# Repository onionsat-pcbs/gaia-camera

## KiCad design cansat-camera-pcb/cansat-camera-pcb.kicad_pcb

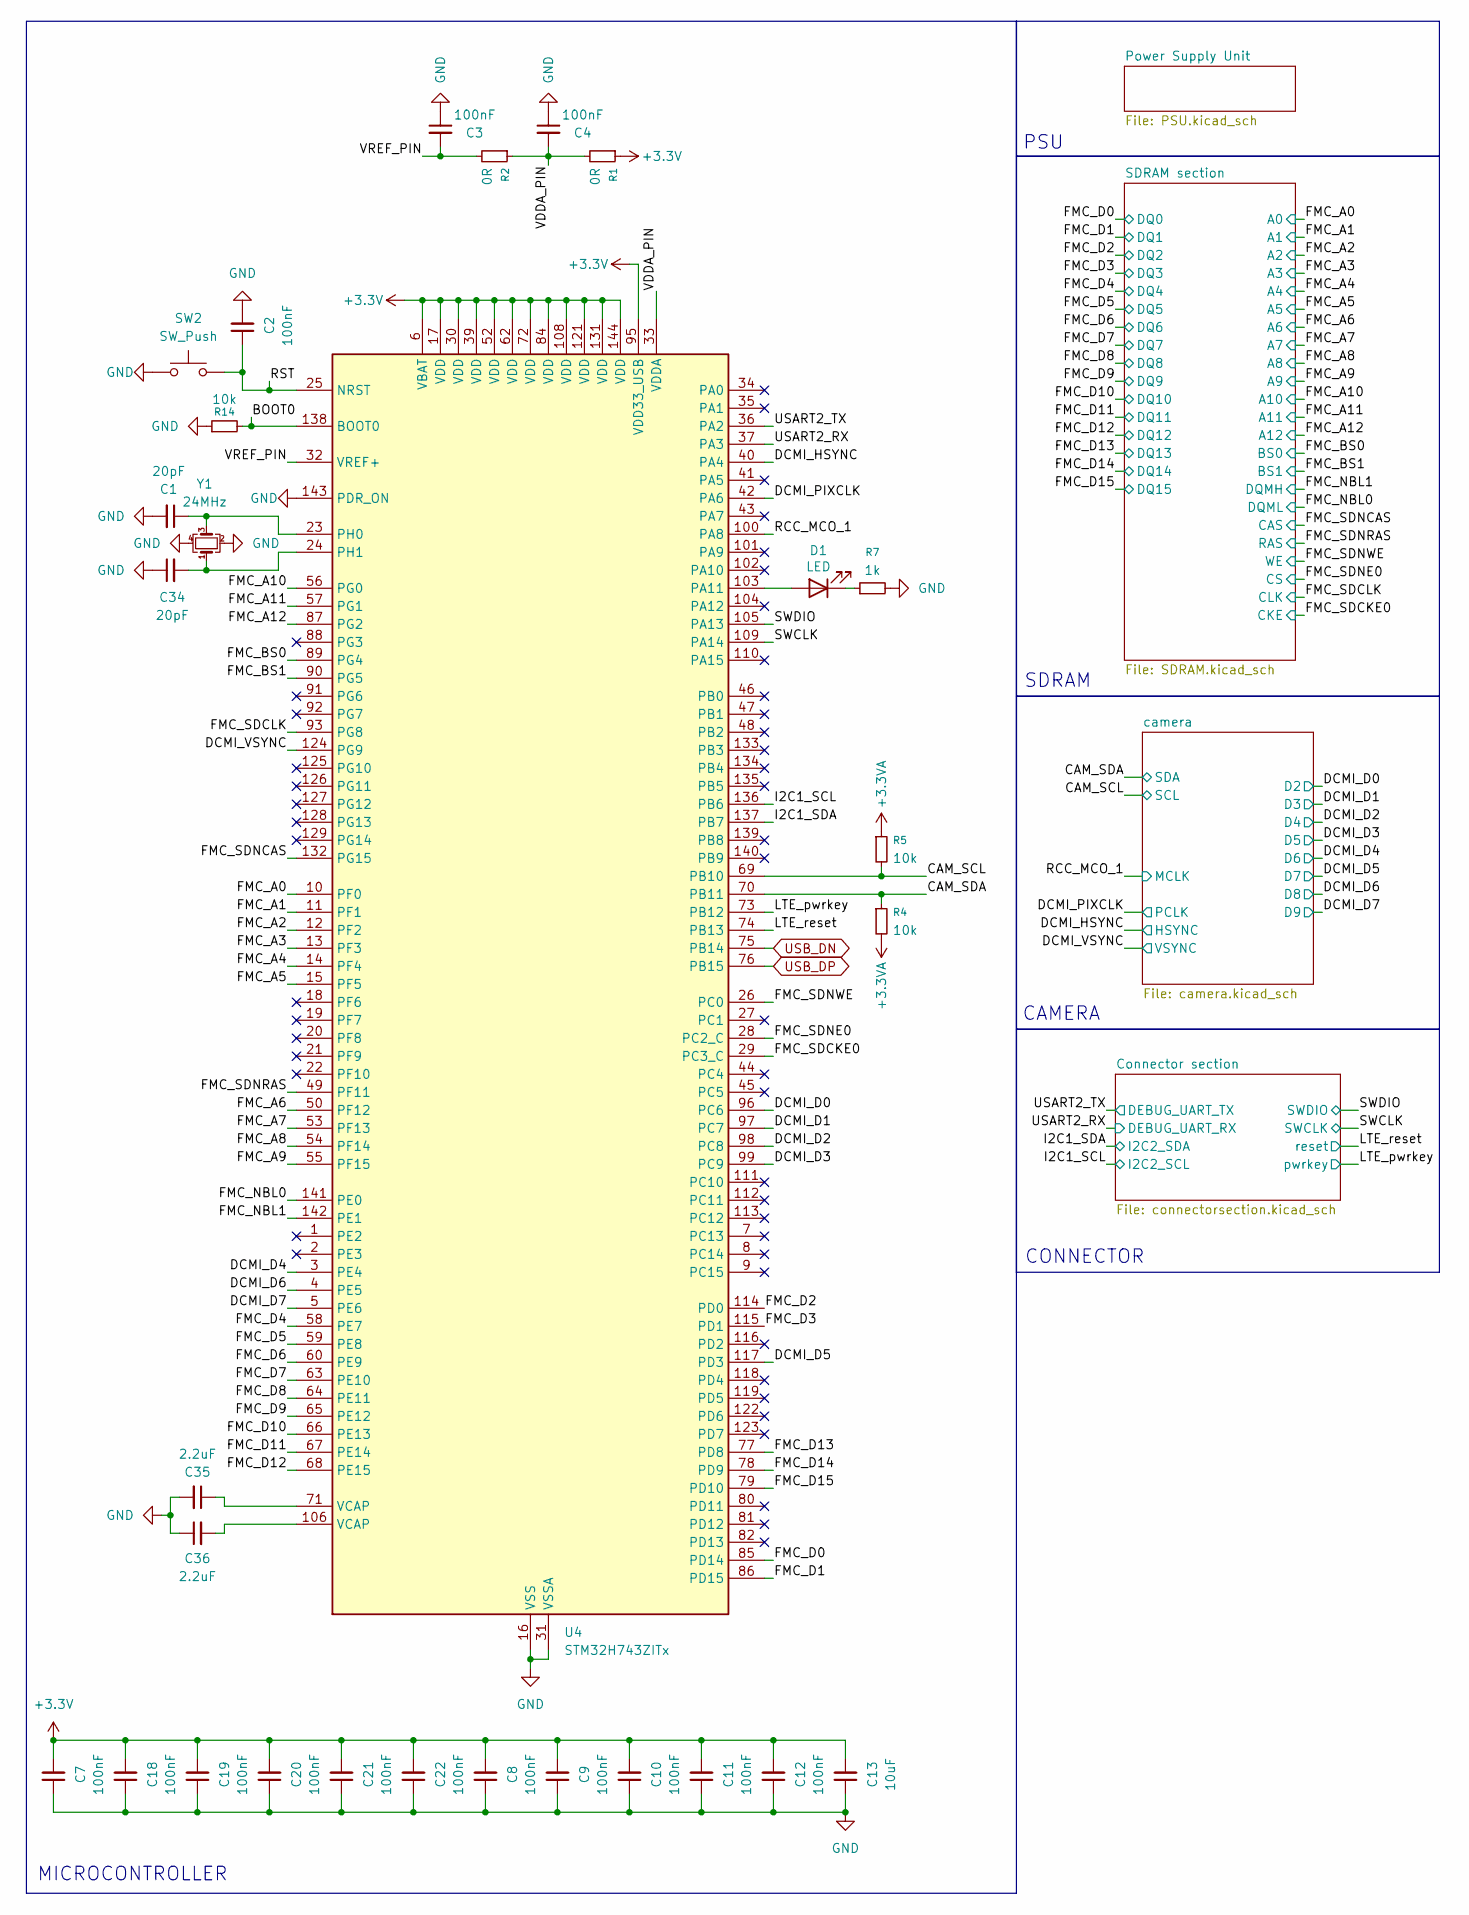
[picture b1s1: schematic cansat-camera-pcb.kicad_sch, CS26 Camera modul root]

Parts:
C1, C34: 20pF; C_0402_1005Metric
C2, C3, C4, C7, C8, C9, C10, C11, C12, C18, C19, C20, C21, C22: 100nF; C_0402_1005Metric
C13: 10uF; C_0603_1608Metric
C35, C36: 2.2uF; C_0603_1608Metric
D1: LED; LED_0603_1608Metric
R1, R2: 0R; R_0402_1005Metric
R4, R5, R14: 10k; R_0402_1005Metric
R7: 1k; R_0603_1608Metric
SW2: SW_Push; KEY-SMD_L4.0-W3.0-LS4.9-1
U4: STM32H743ZITx; LQFP-144_20x20mm_P0.5mm
Y1: 24MHz; Crystal_SMD_3225-4Pin_3.2x2.5mm

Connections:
+3.3V: C7.2, C8.2, C9.2, C10.2, C11.2, C12.2, C13.2, C18.2, C19.2, C20.2, C21.2, C22.2, R1.1, U4.6 (VBAT), U4.17 (VDD), U4.30 (VDD), U4.39 (VDD), U4.52 (VDD), U4.62 (VDD), U4.72 (VDD), U4.84 (VDD), U4.95 (VDD33_USB), U4.108 (VDD), U4.121 (VDD), U4.131 (VDD), U4.144 (VDD); also elsewhere on the board
+3.3VA: R4.2, R5.1; also elsewhere on the board
/BOOT0: R14.2, U4.138 (BOOT0)
/CAM_SCL: R5.2, U4.69 (PB10); also elsewhere on the board
/CAM_SDA: R4.1, U4.70 (PB11); also elsewhere on the board
/DCMI_D0: U4.96 (PC6); also elsewhere on the board
/DCMI_D1: U4.97 (PC7); also elsewhere on the board
/DCMI_D2: U4.98 (PC8); also elsewhere on the board
/DCMI_D3: U4.99 (PC9); also elsewhere on the board
/DCMI_D4: U4.3 (PE4); also elsewhere on the board
/DCMI_D5: U4.117 (PD3); also elsewhere on the board
/DCMI_D6: U4.4 (PE5); also elsewhere on the board
/DCMI_D7: U4.5 (PE6); also elsewhere on the board
/DCMI_HSYNC: U4.40 (PA4); also elsewhere on the board
/DCMI_PIXCLK: U4.42 (PA6); also elsewhere on the board
/DCMI_VSYNC: U4.124 (PG9); also elsewhere on the board
/FMC_A0: U4.10 (PF0); also elsewhere on the board
/FMC_A1: U4.11 (PF1); also elsewhere on the board
/FMC_A2: U4.12 (PF2); also elsewhere on the board
/FMC_A3: U4.13 (PF3); also elsewhere on the board
/FMC_A4: U4.14 (PF4); also elsewhere on the board
/FMC_A5: U4.15 (PF5); also elsewhere on the board
/FMC_A6: U4.50 (PF12); also elsewhere on the board
/FMC_A7: U4.53 (PF13); also elsewhere on the board
/FMC_A8: U4.54 (PF14); also elsewhere on the board
/FMC_A9: U4.55 (PF15); also elsewhere on the board
/FMC_A10: U4.56 (PG0); also elsewhere on the board
/FMC_A11: U4.57 (PG1); also elsewhere on the board
/FMC_A12: U4.87 (PG2); also elsewhere on the board
/FMC_BS0: U4.89 (PG4); also elsewhere on the board
/FMC_BS1: U4.90 (PG5); also elsewhere on the board
/FMC_D0: U4.85 (PD14); also elsewhere on the board
/FMC_D1: U4.86 (PD15); also elsewhere on the board
/FMC_D2: U4.114 (PD0); also elsewhere on the board
/FMC_D3: U4.115 (PD1); also elsewhere on the board
/FMC_D4: U4.58 (PE7); also elsewhere on the board
/FMC_D5: U4.59 (PE8); also elsewhere on the board
/FMC_D6: U4.60 (PE9); also elsewhere on the board
/FMC_D7: U4.63 (PE10); also elsewhere on the board
/FMC_D8: U4.64 (PE11); also elsewhere on the board
/FMC_D9: U4.65 (PE12); also elsewhere on the board
/FMC_D10: U4.66 (PE13); also elsewhere on the board
/FMC_D11: U4.67 (PE14); also elsewhere on the board
/FMC_D12: U4.68 (PE15); also elsewhere on the board
/FMC_D13: U4.77 (PD8); also elsewhere on the board
/FMC_D14: U4.78 (PD9); also elsewhere on the board
/FMC_D15: U4.79 (PD10); also elsewhere on the board
/FMC_NBL0: U4.141 (PE0); also elsewhere on the board
/FMC_NBL1: U4.142 (PE1); also elsewhere on the board
/FMC_SDCKE0: U4.29 (PC3_C); also elsewhere on the board
/FMC_SDCLK: U4.93 (PG8); also elsewhere on the board
/FMC_SDNCAS: U4.132 (PG15); also elsewhere on the board
/FMC_SDNE0: U4.28 (PC2_C); also elsewhere on the board
/FMC_SDNRAS: U4.49 (PF11); also elsewhere on the board
/FMC_SDNWE: U4.26 (PC0); also elsewhere on the board
/I2C1_SCL: U4.136 (PB6); also elsewhere on the board
/I2C1_SDA: U4.137 (PB7); also elsewhere on the board
/LTE_pwrkey: U4.73 (PB12); also elsewhere on the board
/LTE_reset: U4.74 (PB13); also elsewhere on the board
/RCC_MCO_1: U4.100 (PA8); also elsewhere on the board
/RST: C2.1, SW2.2, U4.25 (NRST)
/SWCLK: U4.109 (PA14); also elsewhere on the board
/SWDIO: U4.105 (PA13); also elsewhere on the board
/USART2_RX: U4.37 (PA3); also elsewhere on the board
/USART2_TX: U4.36 (PA2); also elsewhere on the board
/VDDA_PIN: C4.2, R1.2, R2.1, U4.33 (VDDA)
/VREF_PIN: C3.2, R2.2, U4.32 (VREF+)
GND: C1.2, C2.2, C3.1, C4.1, C7.1, C8.1, C9.1, C10.1, C11.1, C12.1, C13.1, C18.1, C19.1, C20.1, C21.1, C22.1, C34.1, C35.2, C36.1, R7.2, R14.1, SW2.1, U4.16 (VSS), U4.31 (VSSA), U4.38 (VSS), U4.51 (VSS), U4.61 (VSS), U4.83 (VSS), U4.94 (VSS), U4.107 (VSS), U4.120 (VSS), U4.130 (VSS), U4.143 (PDR_ON), Y1.2, Y1.4; also elsewhere on the board
unnamed: C35.1, U4.71 (VCAP)
unnamed: C36.2, U4.106 (VCAP)
unnamed: D1.2 (A), U4.103 (PA11)
unnamed: D1.1 (K), R7.1
unnamed: C1.1, U4.23 (PH0), Y1.3
unnamed: C34.2, U4.24 (PH1), Y1.1
USB_DN: U4.75 (PB14); also elsewhere on the board
USB_DP: U4.76 (PB15); also elsewhere on the board

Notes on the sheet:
PSU
SDRAM
MICROCONTROLLER
CAMERA
CONNECTOR

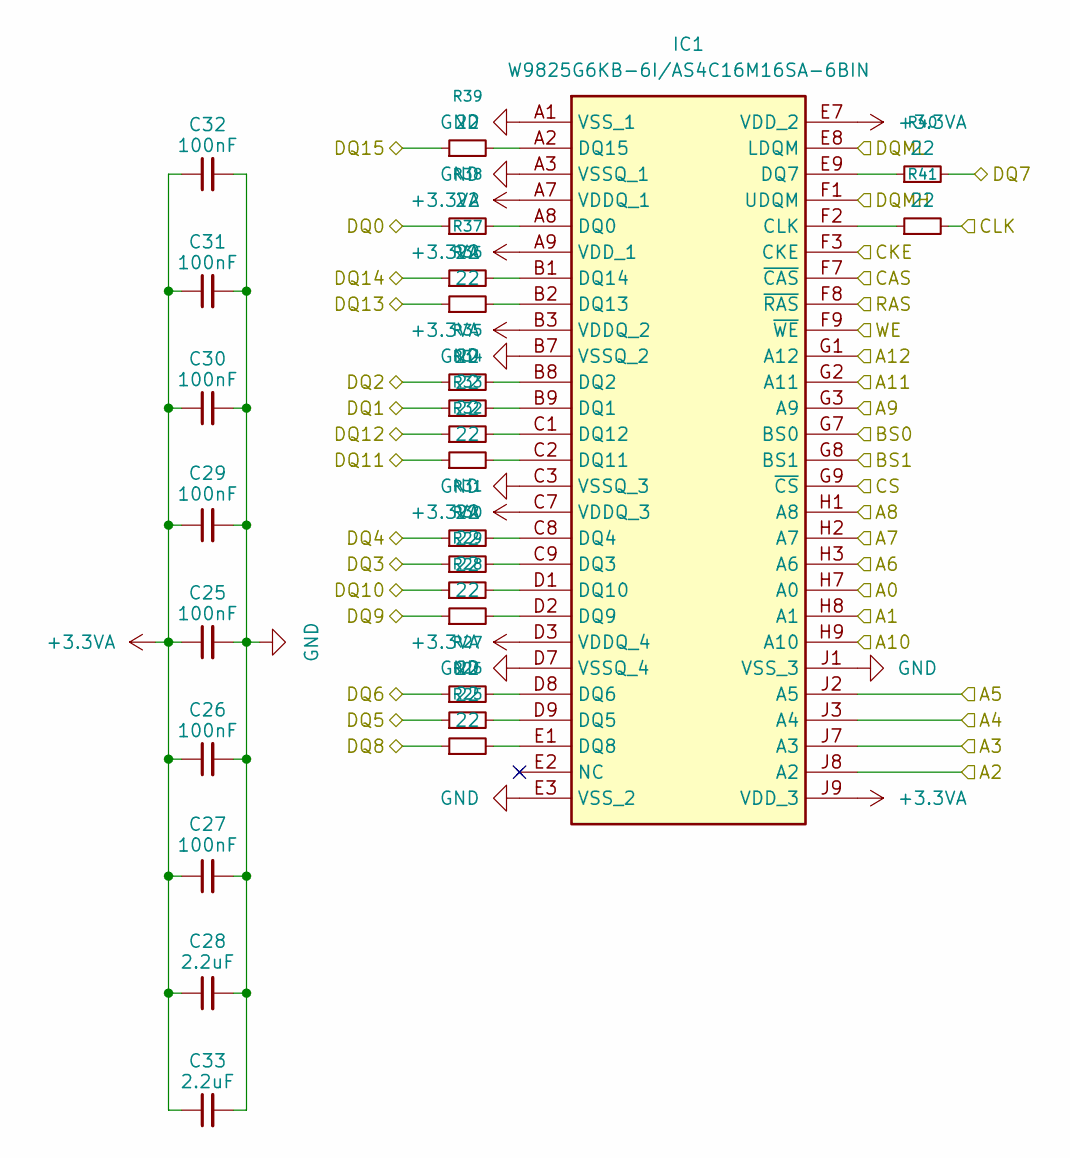
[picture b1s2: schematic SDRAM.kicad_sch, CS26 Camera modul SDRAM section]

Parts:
C25, C26, C27, C29, C30, C31, C32: 100nF; C_0402_1005Metric
C28, C33: 2.2uF; C_0603_1608Metric
IC1: W9825G6KB-6I/AS4C16M16SA-6BIN; Alliance_TFBGA-54_8x8mm_Layout9x9_P0.8mm; Mouser Part Number 454-W9825G6JB-6I
R25, R26, R27, R28, R29, R30, R31, R32, R33, R34, R35, R36, R37, R38, R39, R40, R41: 22; R_0201_0603Metric

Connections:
+3.3VA: C25.1, C26.1, C27.1, C28.1, C29.1, C30.1, C31.1, C32.1, C33.1, IC1.A7 (VDDQ_1), IC1.A9 (VDD_1), IC1.B3 (VDDQ_2), IC1.C7 (VDDQ_3), IC1.D3 (VDDQ_4), IC1.E7 (VDD_2), IC1.J9 (VDD_3); also elsewhere on the board
/FMC_A0: IC1.H7 (A0); also elsewhere on the board
/FMC_A1: IC1.H8 (A1); also elsewhere on the board
/FMC_A2: IC1.J8 (A2); also elsewhere on the board
/FMC_A3: IC1.J7 (A3); also elsewhere on the board
/FMC_A4: IC1.J3 (A4); also elsewhere on the board
/FMC_A5: IC1.J2 (A5); also elsewhere on the board
/FMC_A6: IC1.H3 (A6); also elsewhere on the board
/FMC_A7: IC1.H2 (A7); also elsewhere on the board
/FMC_A8: IC1.H1 (A8); also elsewhere on the board
/FMC_A9: IC1.G3 (A9); also elsewhere on the board
/FMC_A10: IC1.H9 (A10); also elsewhere on the board
/FMC_A11: IC1.G2 (A11); also elsewhere on the board
/FMC_A12: IC1.G1 (A12); also elsewhere on the board
/FMC_BS0: IC1.G7 (BS0); also elsewhere on the board
/FMC_BS1: IC1.G8 (BS1); also elsewhere on the board
/FMC_D0: R38.1; also elsewhere on the board
/FMC_D1: R34.1; also elsewhere on the board
/FMC_D2: R35.1; also elsewhere on the board
/FMC_D3: R30.1; also elsewhere on the board
/FMC_D4: R31.1; also elsewhere on the board
/FMC_D5: R26.1; also elsewhere on the board
/FMC_D6: R27.1; also elsewhere on the board
/FMC_D7: R40.2; also elsewhere on the board
/FMC_D8: R25.1; also elsewhere on the board
/FMC_D9: R28.1; also elsewhere on the board
/FMC_D10: R29.1; also elsewhere on the board
/FMC_D11: R32.1; also elsewhere on the board
/FMC_D12: R33.1; also elsewhere on the board
/FMC_D13: R36.1; also elsewhere on the board
/FMC_D14: R37.1; also elsewhere on the board
/FMC_D15: R39.1; also elsewhere on the board
/FMC_NBL0: IC1.E8 (LDQM); also elsewhere on the board
/FMC_NBL1: IC1.F1 (UDQM); also elsewhere on the board
/FMC_SDCKE0: IC1.F3 (CKE); also elsewhere on the board
/FMC_SDCLK: R41.2; also elsewhere on the board
/FMC_SDNCAS: IC1.F7 (~CAS); also elsewhere on the board
/FMC_SDNE0: IC1.G9 (~CS); also elsewhere on the board
/FMC_SDNRAS: IC1.F8 (~RAS); also elsewhere on the board
/FMC_SDNWE: IC1.F9 (~WE); also elsewhere on the board
GND: C25.2, C26.2, C27.2, C28.2, C29.2, C30.2, C31.2, C32.2, C33.2, IC1.A1 (VSS_1), IC1.A3 (VSSQ_1), IC1.B7 (VSSQ_2), IC1.C3 (VSSQ_3), IC1.D7 (VSSQ_4), IC1.E3 (VSS_2), IC1.J1 (VSS_3); also elsewhere on the board
unnamed: IC1.F2 (CLK), R41.1
unnamed: IC1.A8 (DQ0), R38.2
unnamed: IC1.B9 (DQ1), R34.2
unnamed: IC1.B8 (DQ2), R35.2
unnamed: IC1.C9 (DQ3), R30.2
unnamed: IC1.C8 (DQ4), R31.2
unnamed: IC1.D9 (DQ5), R26.2
unnamed: IC1.D8 (DQ6), R27.2
unnamed: IC1.E9 (DQ7), R40.1
unnamed: IC1.E1 (DQ8), R25.2
unnamed: IC1.D2 (DQ9), R28.2
unnamed: IC1.D1 (DQ10), R29.2
unnamed: IC1.C2 (DQ11), R32.2
unnamed: IC1.C1 (DQ12), R33.2
unnamed: IC1.B2 (DQ13), R36.2
unnamed: IC1.B1 (DQ14), R37.2
unnamed: IC1.A2 (DQ15), R39.2

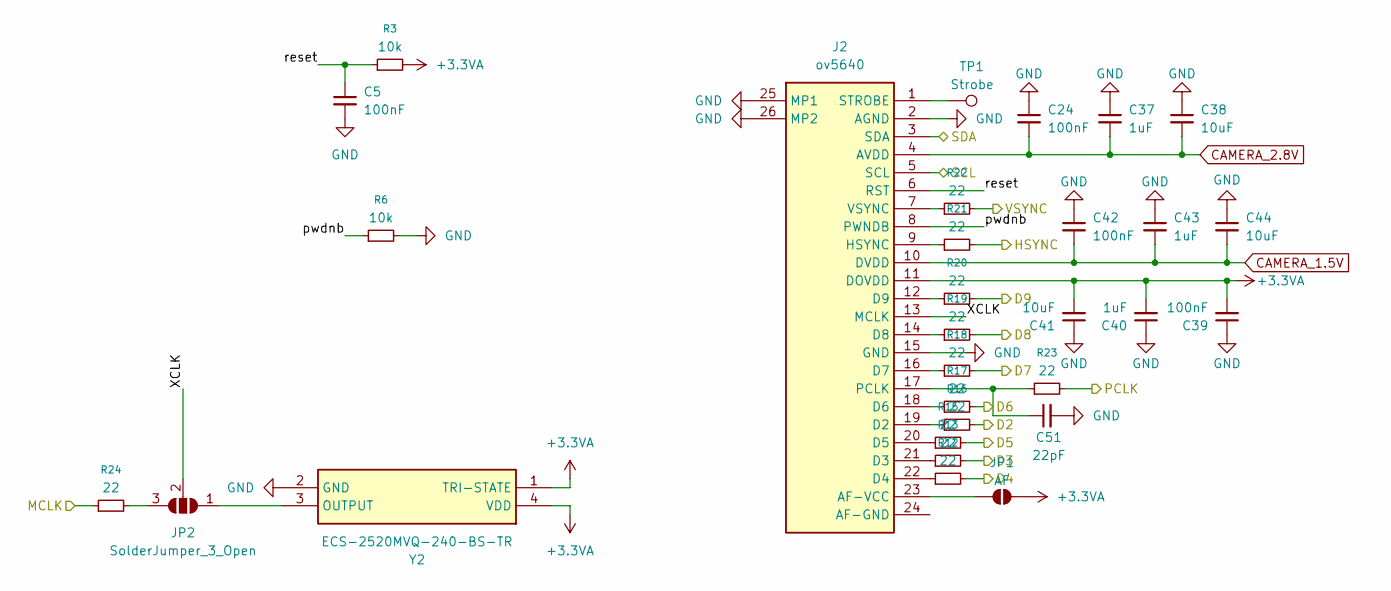
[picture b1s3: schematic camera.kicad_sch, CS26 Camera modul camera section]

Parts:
C5, C24, C39, C42: 100nF; C_0402_1005Metric
C37, C40, C43: 1uF; C_0603_1608Metric
C38, C41, C44: 10uF; C_0603_1608Metric
C51: 22pF; C_0402_1005Metric
J2: ov5640; F33Z1A7Q1E8C24; Manufacturer_Part_Number F33Z-1A7Q1-E8C24
JP1: AF; SolderJumper-2_P1.3mm_Open_Pad1.0x1.5mm
JP2: SolderJumper_3_Open; SolderJumper-3_P1.3mm_Open_Pad1.0x1.5mm
R3, R6: 10k; R_0402_1005Metric
R12, R13, R15, R16, R17, R18, R19, R20, R21, R22, R23, R24: 22; R_0201_0603Metric
TP1: Strobe; TestPoint_Pad_1.5x1.5mm
Y2: ECS-2520MVQ-240-BS-TR; ECS2520MVQ240BSTR; Mouser Part Number 520-E2520MVQ240BSTR

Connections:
+3.3VA: C39.2, C40.2, C41.2, J2.11 (DOVDD), JP1.2 (B), R3.2, Y2.1 (TRI-STATE), Y2.4 (VDD); also elsewhere on the board
/CAM_SCL: J2.5 (SCL); also elsewhere on the board
/CAM_SDA: J2.3 (SDA); also elsewhere on the board
/DCMI_D0: R16.2; also elsewhere on the board
/DCMI_D1: R13.2; also elsewhere on the board
/DCMI_D2: R12.2; also elsewhere on the board
/DCMI_D3: R15.2; also elsewhere on the board
/DCMI_D4: R17.2; also elsewhere on the board
/DCMI_D5: R18.2; also elsewhere on the board
/DCMI_D6: R19.2; also elsewhere on the board
/DCMI_D7: R20.2; also elsewhere on the board
/DCMI_HSYNC: R21.2; also elsewhere on the board
/DCMI_PIXCLK: R23.2; also elsewhere on the board
/DCMI_VSYNC: R22.2; also elsewhere on the board
/RCC_MCO_1: R24.1; also elsewhere on the board
/camera/XCLK: J2.13 (MCLK), JP2.2 (C)
/camera/pwdnb: J2.8 (PWNDB), R6.1
/camera/reset: C5.1, J2.6 (RST), R3.1
CAMERA_1.5V: C42.2, C43.2, C44.2, J2.10 (DVDD); also elsewhere on the board
CAMERA_2.8V: C24.2, C37.2, C38.2, J2.4 (AVDD); also elsewhere on the board
GND: C5.2, C24.1, C37.1, C38.1, C39.1, C40.1, C41.1, C42.1, C43.1, C44.1, C51.2, J2.2 (AGND), J2.15 (GND), J2.25 (MP1), J2.26 (MP2), R6.2, Y2.2 (GND); also elsewhere on the board
unnamed: J2.23 (AF-VCC), JP1.1 (A)
unnamed: J2.19 (D2), R16.1
unnamed: J2.21 (D3), R13.1
unnamed: J2.22 (D4), R12.1
unnamed: J2.20 (D5), R15.1
unnamed: J2.18 (D6), R17.1
unnamed: J2.16 (D7), R18.1
unnamed: J2.14 (D8), R19.1
unnamed: J2.12 (D9), R20.1
unnamed: J2.9 (HSYNC), R21.1
unnamed: C51.1, J2.17 (PCLK), R23.1
unnamed: J2.1 (STROBE), TP1.1
unnamed: J2.7 (VSYNC), R22.1
unnamed: JP2.1 (A), Y2.3 (OUTPUT)
unnamed: JP2.3 (B), R24.2

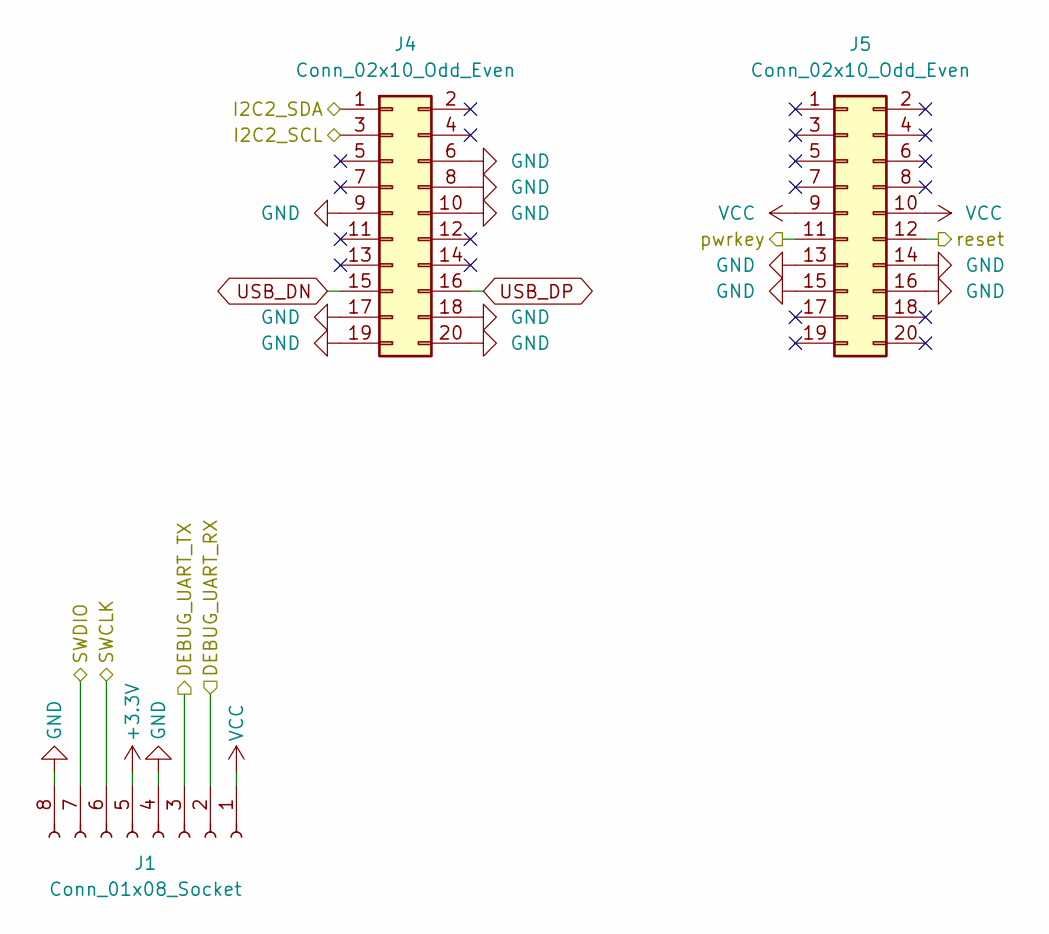
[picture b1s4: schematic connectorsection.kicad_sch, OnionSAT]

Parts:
J1: Conn_01x08_Socket; HDR-SMD_8P-P2.00-H-F-W9.2
J4, J5: Conn_02x10_Odd_Even; PinHeader_2x10_P2.00mm_Vertical_SMD

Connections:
+3.3V: J1.5; also elsewhere on the board
/I2C1_SCL: J4.3; also elsewhere on the board
/I2C1_SDA: J4.1; also elsewhere on the board
/LTE_pwrkey: J5.11; also elsewhere on the board
/LTE_reset: J5.12; also elsewhere on the board
/SWCLK: J1.6; also elsewhere on the board
/SWDIO: J1.7; also elsewhere on the board
/USART2_RX: J1.2; also elsewhere on the board
/USART2_TX: J1.3; also elsewhere on the board
GND: J1.4, J1.8, J4.6, J4.8, J4.9, J4.10, J4.17, J4.18, J4.19, J4.20, J5.13, J5.14, J5.15, J5.16; also elsewhere on the board
USB_DN: J4.15; also elsewhere on the board
USB_DP: J4.16; also elsewhere on the board
VCC: J1.1, J5.9, J5.10; also elsewhere on the board

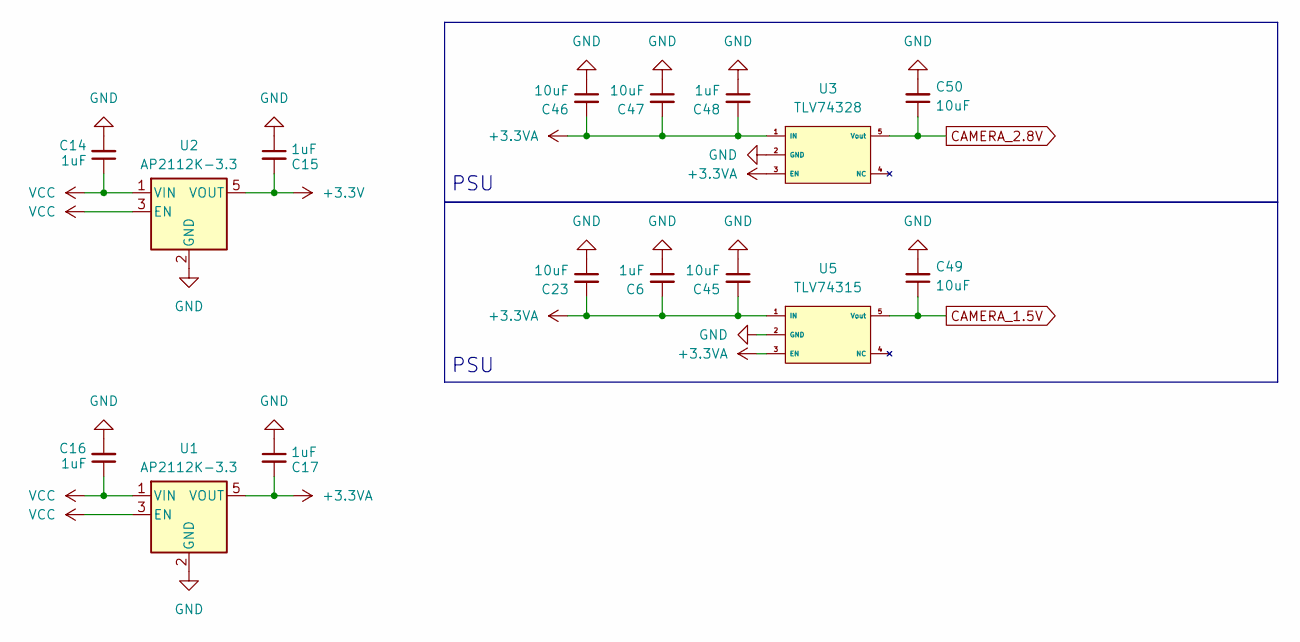
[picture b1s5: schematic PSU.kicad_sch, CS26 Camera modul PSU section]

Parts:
C6, C14, C15, C16, C17, C48: 1uF; C_0603_1608Metric
C23, C45, C46, C47, C49, C50: 10uF; C_0603_1608Metric
U1, U2: AP2112K-3.3; SOT-23-5
U3: TLV74328; SOT-23-5
U5: TLV74315; SOT-23-5

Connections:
+3.3V: C15.2, U2.5 (VOUT); also elsewhere on the board
+3.3VA: C6.2, C17.2, C23.2, C45.2, C46.2, C47.2, C48.2, U1.5 (VOUT), U3.1 (IN), U3.3 (EN), U5.1 (IN), U5.3 (EN); also elsewhere on the board
CAMERA_1.5V: C49.1, U5.5 (Vout); also elsewhere on the board
CAMERA_2.8V: C50.1, U3.5 (Vout); also elsewhere on the board
GND: C6.1, C14.2, C15.1, C16.2, C17.1, C23.1, C45.1, C46.1, C47.1, C48.1, C49.2, C50.2, U1.2 (GND), U2.2 (GND), U3.2 (GND), U5.2 (GND); also elsewhere on the board
VCC: C14.1, C16.1, U1.1 (VIN), U1.3 (EN), U2.1 (VIN), U2.3 (EN); also elsewhere on the board

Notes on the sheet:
PSU

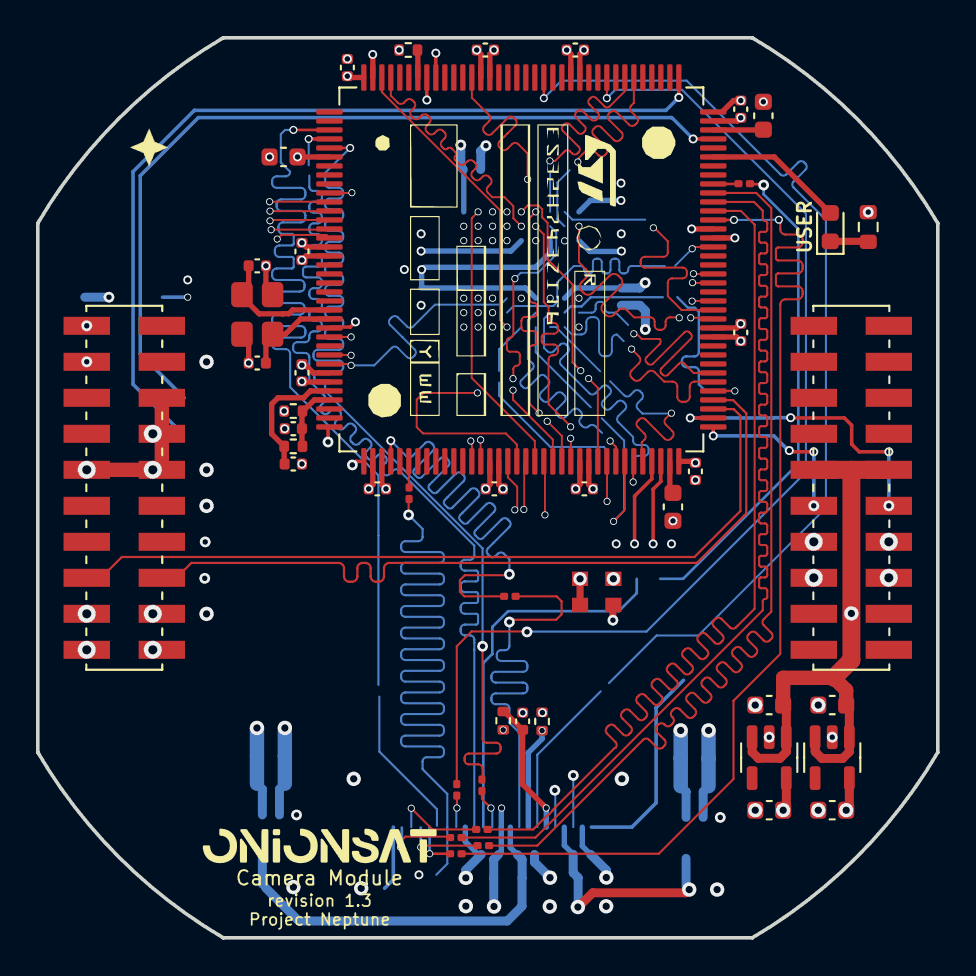
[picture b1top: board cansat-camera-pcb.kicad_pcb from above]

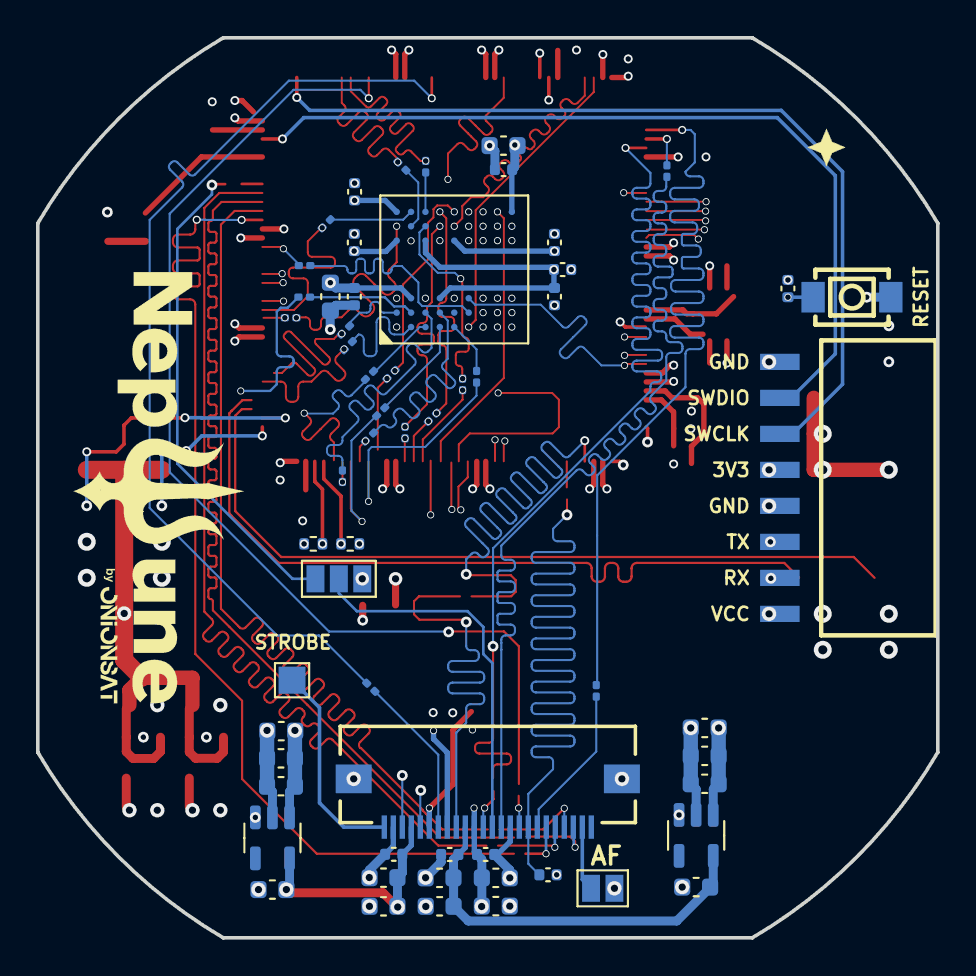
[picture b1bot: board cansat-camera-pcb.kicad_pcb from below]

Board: 8 copper layers, 50.0 x 50.0 mm, 105 parts (59 on the bottom side), 114 nets.

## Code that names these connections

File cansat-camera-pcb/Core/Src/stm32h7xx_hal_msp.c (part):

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    __HAL_RCC_GPIOD_CLK_ENABLE();
    __HAL_RCC_GPIOG_CLK_ENABLE();
    /**DCMI GPIO Configuration
    PE4     ------> DCMI_D4
    PE5     ------> DCMI_D6
    PE6     ------> DCMI_D7
    PA4     ------> DCMI_HSYNC
    PA6     ------> DCMI_PIXCLK
    PC6     ------> DCMI_D0
    PC7     ------> DCMI_D1
    PC8     ------> DCMI_D2
    PC9     ------> DCMI_D3
    PD3     ------> DCMI_D5
    PG9     ------> DCMI_VSYNC
    */
    GPIO_InitStruct.Pin = GPIO_PIN_4|GPIO_PIN_5|GPIO_PIN_6;
    GPIO_InitStruct.Mode = GPIO_MODE_AF_PP;
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    __HAL_RCC_DCMI_CLK_DISABLE();

    /**DCMI GPIO Configuration
    PE4     ------> DCMI_D4
    PE5     ------> DCMI_D6
    PE6     ------> DCMI_D7
    PA4     ------> DCMI_HSYNC
    PA6     ------> DCMI_PIXCLK
    PC6     ------> DCMI_D0
    PC7     ------> DCMI_D1
    PC8     ------> DCMI_D2
    PC9     ------> DCMI_D3
    PD3     ------> DCMI_D5
    PG9     ------> DCMI_VSYNC
    */
    HAL_GPIO_DeInit(GPIOE, GPIO_PIN_4|GPIO_PIN_5|GPIO_PIN_6);

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
    __HAL_RCC_GPIOB_CLK_ENABLE();
    /**I2C1 GPIO Configuration
    PB6     ------> I2C1_SCL
    PB7     ------> I2C1_SDA
    */
    GPIO_InitStruct.Pin = GPIO_PIN_6|GPIO_PIN_7;
    GPIO_InitStruct.Mode = GPIO_MODE_AF_OD;
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
    __HAL_RCC_GPIOB_CLK_ENABLE();
    /**I2C2 GPIO Configuration
    PB10     ------> I2C2_SCL
    PB11     ------> I2C2_SDA
    */
    GPIO_InitStruct.Pin = GPIO_PIN_10|GPIO_PIN_11;
    GPIO_InitStruct.Mode = GPIO_MODE_AF_OD;
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    __HAL_RCC_I2C1_CLK_DISABLE();

    /**I2C1 GPIO Configuration
    PB6     ------> I2C1_SCL
    PB7     ------> I2C1_SDA
    */
    HAL_GPIO_DeInit(GPIOB, GPIO_PIN_6);

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    __HAL_RCC_I2C2_CLK_DISABLE();

    /**I2C2 GPIO Configuration
    PB10     ------> I2C2_SCL
    PB11     ------> I2C2_SDA
    */
    HAL_GPIO_DeInit(GPIOB, GPIO_PIN_10);

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
    __HAL_RCC_GPIOA_CLK_ENABLE();
    /**USART2 GPIO Configuration
    PA2     ------> USART2_TX
    PA3     ------> USART2_RX
    */
    GPIO_InitStruct.Pin = GPIO_PIN_2|GPIO_PIN_3;
    GPIO_InitStruct.Mode = GPIO_MODE_AF_PP;
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    __HAL_RCC_USART2_CLK_DISABLE();

    /**USART2 GPIO Configuration
    PA2     ------> USART2_TX
    PA3     ------> USART2_RX
    */
    HAL_GPIO_DeInit(GPIOA, GPIO_PIN_2|GPIO_PIN_3);

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
    __HAL_RCC_GPIOB_CLK_ENABLE();
    /**USB_OTG_HS GPIO Configuration
    PB14     ------> USB_OTG_HS_DM
    PB15     ------> USB_OTG_HS_DP
    */
    GPIO_InitStruct.Pin = GPIO_PIN_14|GPIO_PIN_15;
    GPIO_InitStruct.Mode = GPIO_MODE_AF_PP;
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    __HAL_RCC_USB_OTG_HS_CLK_DISABLE();

    /**USB_OTG_HS GPIO Configuration
    PB14     ------> USB_OTG_HS_DM
    PB15     ------> USB_OTG_HS_DP
    */
    HAL_GPIO_DeInit(GPIOB, GPIO_PIN_14|GPIO_PIN_15);

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  __HAL_RCC_FMC_CLK_ENABLE();

  /** FMC GPIO Configuration
  PF0   ------> FMC_A0
  PF1   ------> FMC_A1
  PF2   ------> FMC_A2
  PF3   ------> FMC_A3
  PF4   ------> FMC_A4
  PF5   ------> FMC_A5
  PC0   ------> FMC_SDNWE
  PC2_C   ------> FMC_SDNE0
  PC3_C   ------> FMC_SDCKE0
  PF11   ------> FMC_SDNRAS
  PF12   ------> FMC_A6
  PF13   ------> FMC_A7
  PF14   ------> FMC_A8
  PF15   ------> FMC_A9
  PG0   ------> FMC_A10
  PG1   ------> FMC_A11
  PE7   ------> FMC_D4
  PE8   ------> FMC_D5
  PE9   ------> FMC_D6
  PE10   ------> FMC_D7
  PE11   ------> FMC_D8
  PE12   ------> FMC_D9
  PE13   ------> FMC_D10
  PE14   ------> FMC_D11
  PE15   ------> FMC_D12
  PD8   ------> FMC_D13
  PD9   ------> FMC_D14
  PD10   ------> FMC_D15
  PD14   ------> FMC_D0
  PD15   ------> FMC_D1
  PG2   ------> FMC_A12
  PG4   ------> FMC_BA0
  PG5   ------> FMC_BA1
  PG8   ------> FMC_SDCLK
  PD0   ------> FMC_D2
  PD1   ------> FMC_D3
  PG15   ------> FMC_SDNCAS
  PE0   ------> FMC_NBL0
  PE1   ------> FMC_NBL1
  */
  GPIO_InitStruct.Pin = GPIO_PIN_0|GPIO_PIN_1|GPIO_PIN_2|GPIO_PIN_3
                          |GPIO_PIN_4|GPIO_PIN_5|GPIO_PIN_11|GPIO_PIN_12
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  __HAL_RCC_FMC_CLK_DISABLE();

  /** FMC GPIO Configuration
  PF0   ------> FMC_A0
  PF1   ------> FMC_A1
  PF2   ------> FMC_A2
  PF3   ------> FMC_A3
  PF4   ------> FMC_A4
  PF5   ------> FMC_A5
  PC0   ------> FMC_SDNWE
  PC2_C   ------> FMC_SDNE0
  PC3_C   ------> FMC_SDCKE0
  PF11   ------> FMC_SDNRAS
  PF12   ------> FMC_A6
  PF13   ------> FMC_A7
  PF14   ------> FMC_A8
  PF15   ------> FMC_A9
  PG0   ------> FMC_A10
  PG1   ------> FMC_A11
  PE7   ------> FMC_D4
  PE8   ------> FMC_D5
  PE9   ------> FMC_D6
  PE10   ------> FMC_D7
  PE11   ------> FMC_D8
  PE12   ------> FMC_D9
  PE13   ------> FMC_D10
  PE14   ------> FMC_D11
  PE15   ------> FMC_D12
  PD8   ------> FMC_D13
  PD9   ------> FMC_D14
  PD10   ------> FMC_D15
  PD14   ------> FMC_D0
  PD15   ------> FMC_D1
  PG2   ------> FMC_A12
  PG4   ------> FMC_BA0
  PG5   ------> FMC_BA1
  PG8   ------> FMC_SDCLK
  PD0   ------> FMC_D2
  PD1   ------> FMC_D3
  PG15   ------> FMC_SDNCAS
  PE0   ------> FMC_NBL0
  PE1   ------> FMC_NBL1
  */
  HAL_GPIO_DeInit(GPIOF, GPIO_PIN_0|GPIO_PIN_1|GPIO_PIN_2|GPIO_PIN_3
                          |GPIO_PIN_4|GPIO_PIN_5|GPIO_PIN_11|GPIO_PIN_12
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
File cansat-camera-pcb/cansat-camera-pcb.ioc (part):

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Mcu.Name=STM32H743ZITx
Mcu.Package=LQFP144
Mcu.UserName=STM32H743ZITx
PA11.Signal=GPIO_Output
PA13\ (JTMS/SWDIO).Mode=Serial_Wire
PA13\ (JTMS/SWDIO).Signal=DEBUG_JTMS-SWDIO
PA14\ (JTCK/SWCLK).Mode=Serial_Wire
PA14\ (JTCK/SWCLK).Signal=DEBUG_JTCK-SWCLK
PA2.Mode=Asynchronous
PA2.Signal=USART2_TX
PA3.Mode=Asynchronous
PA3.Signal=USART2_RX
PA4.Mode=Slave_8_bits_External_Synchro
PA4.Signal=DCMI_HSYNC
PA6.Mode=Slave_8_bits_External_Synchro
PA6.Signal=DCMI_PIXCLK
PA8.Mode=Clock-out-1
PA8.Signal=RCC_MCO_1
PB10.Mode=I2C
PB10.Signal=I2C2_SCL
PB11.Mode=I2C
PB11.Signal=I2C2_SDA
PB12.Signal=GPIO_Output
PB13.Signal=GPIO_Output
PB14.Mode=Host_FS
PB14.Signal=USB_OTG_HS_DM
PB15.Mode=Host_FS
PB15.Signal=USB_OTG_HS_DP
PB6.Mode=I2C
PB6.Signal=I2C1_SCL
PB7.Mode=I2C
PB7.Signal=I2C1_SDA
PC0.Signal=FMC_SDNWE
PC2_C.Mode=SdramChipSelect1_1
PC2_C.Signal=FMC_SDNE0
PC3_C.Mode=SdramChipSelect1_1
PC3_C.Signal=FMC_SDCKE0
PC6.Mode=Slave_8_bits_External_Synchro
PC6.Signal=DCMI_D0
PC7.Mode=Slave_8_bits_External_Synchro
PC7.Signal=DCMI_D1
PC8.Mode=Slave_8_bits_External_Synchro
PC8.Signal=DCMI_D2
PC9.Mode=Slave_8_bits_External_Synchro
PC9.Signal=DCMI_D3
PD0.Signal=FMC_D2_DA2
PD1.Signal=FMC_D3_DA3
PD10.Signal=FMC_D15_DA15
PD14.Signal=FMC_D0_DA0
PD15.Signal=FMC_D1_DA1
PD3.Mode=Slave_8_bits_External_Synchro
PD3.Signal=DCMI_D5
PD8.Signal=FMC_D13_DA13
PD9.Signal=FMC_D14_DA14
PE0.Signal=FMC_NBL0
PE1.Signal=FMC_NBL1
PE10.Signal=FMC_D7_DA7
PE11.Signal=FMC_D8_DA8
PE12.Signal=FMC_D9_DA9
PE13.Signal=FMC_D10_DA10
PE14.Signal=FMC_D11_DA11
PE15.Signal=FMC_D12_DA12
PE4.Mode=Slave_8_bits_External_Synchro
PE4.Signal=DCMI_D4
PE5.Mode=Slave_8_bits_External_Synchro
PE5.Signal=DCMI_D6
PE6.Mode=Slave_8_bits_External_Synchro
PE6.Signal=DCMI_D7
PE7.Signal=FMC_D4_DA4
PE8.Signal=FMC_D5_DA5
PE9.Signal=FMC_D6_DA6
PF0.Signal=FMC_A0
PF1.Signal=FMC_A1
PF11.Signal=FMC_SDNRAS
PF12.Signal=FMC_A6
PF13.Signal=FMC_A7
PF14.Signal=FMC_A8
PF15.Signal=FMC_A9
PF2.Signal=FMC_A2
PF3.Signal=FMC_A3
PF4.Signal=FMC_A4
PF5.Signal=FMC_A5
PG0.Signal=FMC_A10
PG1.Signal=FMC_A11
PG15.Signal=FMC_SDNCAS
PG2.Signal=FMC_A12
PG4.Signal=FMC_A14_BA0
PG5.Signal=FMC_A15_BA1
PG8.Signal=FMC_SDCLK
PG9.Mode=Slave_8_bits_External_Synchro
PG9.Signal=DCMI_VSYNC
PH0-OSC_IN\ (PH0).Mode=HSE-External-Oscillator
PH0-OSC_IN\ (PH0).Signal=RCC_OSC_IN
PH1-OSC_OUT\ (PH1).Mode=HSE-External-Oscillator
PH1-OSC_OUT\ (PH1).Signal=RCC_OSC_OUT
RCC.SYSCLKFreq_VALUE=64000000
board=custom

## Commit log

2025-08-06 initial relase
2025-08-06 buzikaaaaaaaa
2025-08-11 -4g modul(4g modul on other pcb)
2025-08-12 Footprint assign
2025-08-12 Revert "Footprint assign"
    This reverts commit b0d58344ac617605db2b6635d18d5284d5b3f755.
2025-08-13 Footprint assign
    Reset kivételével minden hozzácsatolva
2025-08-13 button footprint added to library and assigned
2025-08-13 Footprint assign final
2025-08-14 Alkatrész elhelyezés final
2025-08-17 Sdram finish, stm részben
2025-08-18 Routing tisztázás (sdram, stm)
2025-08-19 Stm32, Sdram routolás végleges
2025-08-21 Routolás folytatása
2025-08-25 new sdram added, some routing
    sdram added to both footprint library and symbol library
2025-08-25 Routing+SDram csere
2025-08-26 Routolás SDkártya
2025-08-30 ready
2025-08-30 USB fix
2025-09-06 bga sdram added
2025-09-06 Routolás sdram
2025-09-08 sdcard deleted form this PCB
2025-09-16 Stiching vias
2025-09-16 fixes
2025-09-18 adding onionsat to silkscreen
2025-09-28 Sdram finish, cleanup
2025-09-28 Cleanup finish
2025-10-04 Camera_Final
2025-10-05 some fixes
2025-10-05 Regulator+
2025-10-08 adding heatsink+small fixes
2025-10-08 send to production
2026-01-03 3d models
2026-01-07 fixing 3d models
2026-01-19 dagobert bácsi hegyekben a steksz
2026-01-19 Sdram reroute
    Nem több mint a cím
2026-01-20 Sdram route
    sdram reroute
2026-01-25 milan eszi a havat(unicummal) (jonas is zabalja)
2026-01-25 Finish
    Vége
2026-01-26 1.1 - production
2026-02-28 Reroute
    Robinak fenomenális buksija van
2026-02-28 Reroute
    BUksi
2026-03-01 Fixes SDRAM, routing (1/2)
2026-03-01 CODEGEN + finishing SDRAM routing
2026-03-01 OV5640 routing start
2026-03-01 Finish routing
2026-03-01 adding stm orientation mark
2026-03-01 Fixing routing problems
2026-03-02 Production v1.3+1.2

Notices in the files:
cansat-camera-pcb/Core/Src/stm32h7xx_hal_msp.c:
Copyright (c) 2026 STMicroelectronics.
All rights reserved.
This software is licensed under terms that can be found in the LICENSE file
